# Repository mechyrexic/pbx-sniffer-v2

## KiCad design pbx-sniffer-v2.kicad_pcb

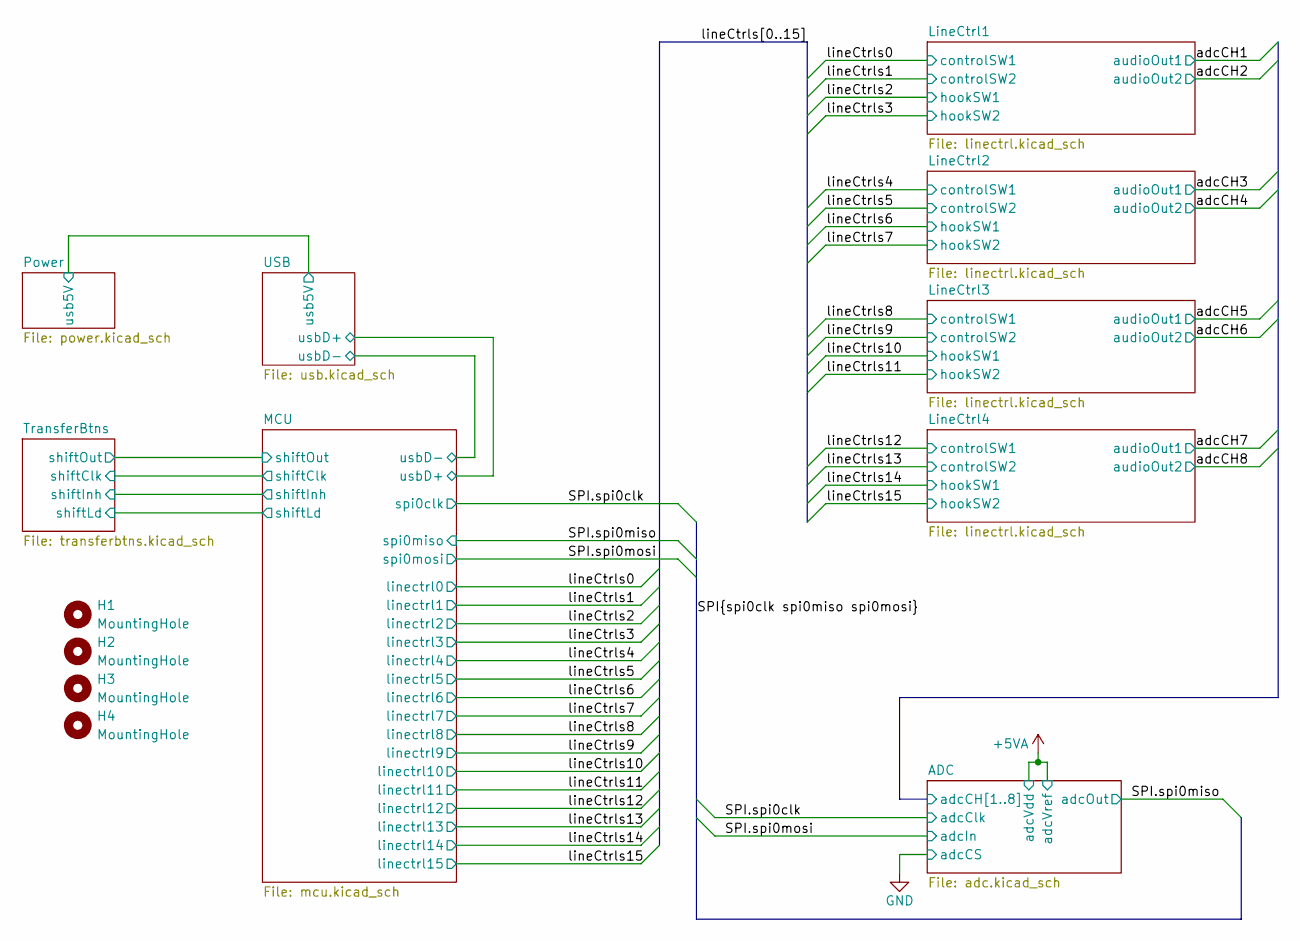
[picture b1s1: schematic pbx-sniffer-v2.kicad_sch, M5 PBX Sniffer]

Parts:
H1, H2, H3, H4: MountingHole; MountingHole_5.3mm_M5_Pad

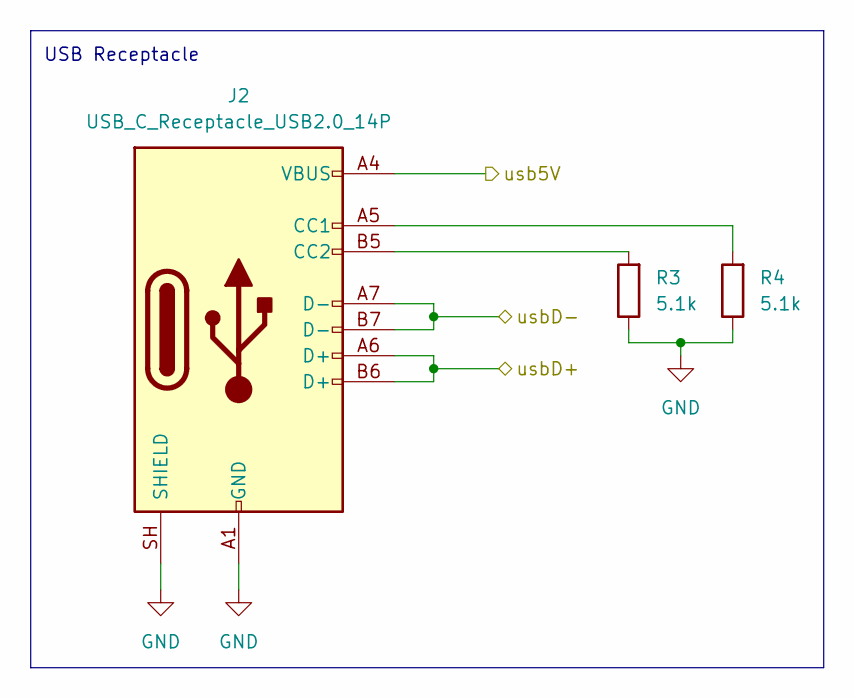
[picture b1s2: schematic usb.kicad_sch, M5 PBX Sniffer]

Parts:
J2: USB_C_Receptacle_USB2.0_14P; USB_C_Receptacle_Amphenol_12401610E4-2A
R3, R4: 5.1k; R_0805_2012Metric

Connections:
/MCU/usbD+: J2.A6 (D+), J2.B6 (D+); also elsewhere on the board
/MCU/usbD-: J2.A7 (D-), J2.B7 (D-); also elsewhere on the board
/Power/usb5V: J2.A4 (VBUS), J2.A9 (VBUS), J2.B4 (VBUS), J2.B9 (VBUS); also elsewhere on the board
GND: J2.A1 (GND), J2.A12 (GND), J2.B1 (GND), J2.B12 (GND), J2.SH (SHIELD), R3.1, R4.1; also elsewhere on the board
unnamed: J2.A5 (CC1), R4.2
unnamed: J2.B5 (CC2), R3.2

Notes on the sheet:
USB Receptacle

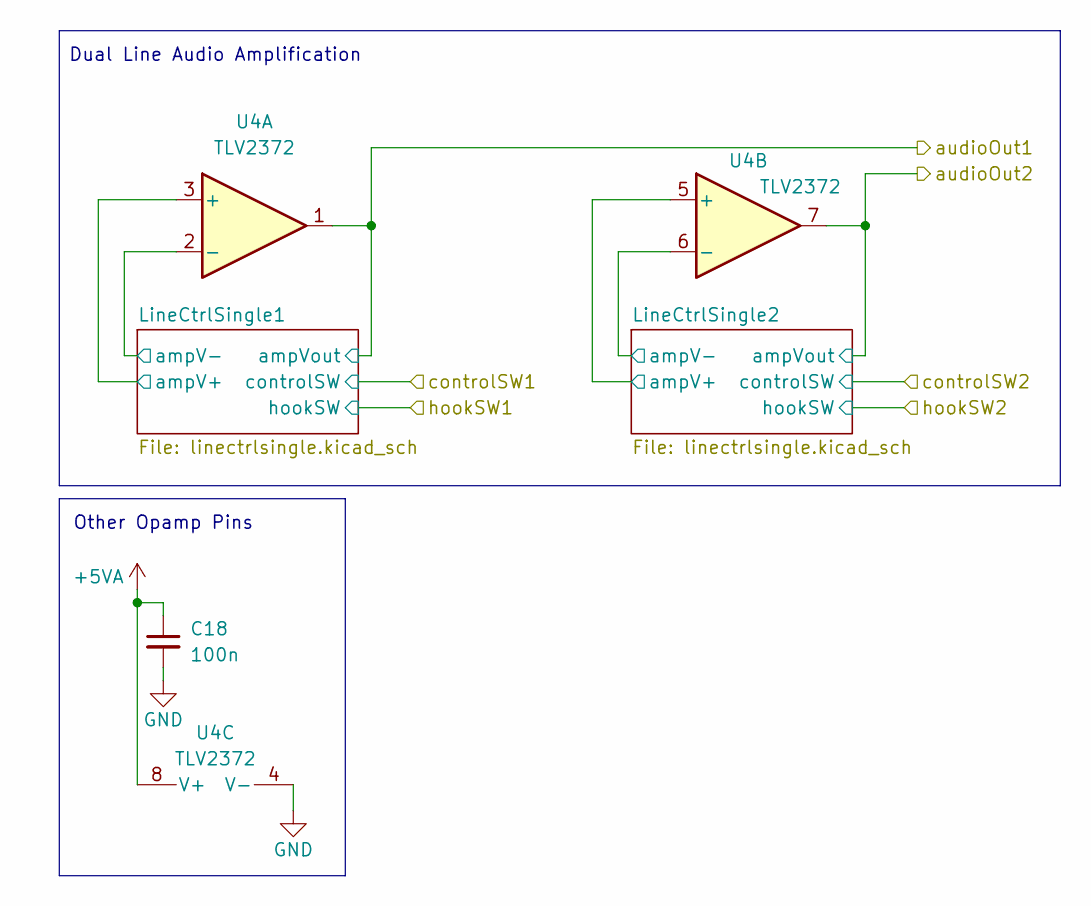
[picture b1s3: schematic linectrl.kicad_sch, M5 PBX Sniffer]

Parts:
C18: 100n; C_0805_2012Metric
U4: TLV2372; SOIC-8_3.9x4.9mm_P1.27mm

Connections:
+5VA: C18.1, U4.8 (V+); also elsewhere on the board
/ADC/adcCH1: U4.1; also elsewhere on the board
/ADC/adcCH2: U4.7; also elsewhere on the board
/LineCtrl1/LineCtrlSingle1/ampV+: U4.3 (+); also elsewhere on the board
/LineCtrl1/LineCtrlSingle1/ampV-: U4.2 (-); also elsewhere on the board
/LineCtrl1/LineCtrlSingle2/ampV+: U4.5 (+); also elsewhere on the board
/LineCtrl1/LineCtrlSingle2/ampV-: U4.6 (-); also elsewhere on the board
GND: C18.2, U4.4 (V-); also elsewhere on the board

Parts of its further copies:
C25, C32, C39: 100n; C_0805_2012Metric
U5, U6, U7: TLV2372; SOIC-8_3.9x4.9mm_P1.27mm

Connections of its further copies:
+5VA: C25.1, C32.1, C39.1, U5.8 (V+), U6.8 (V+), U7.8 (V+); also elsewhere on the board
/ADC/adcCH3: U5.1; also elsewhere on the board
/ADC/adcCH4: U5.7; also elsewhere on the board
/ADC/adcCH5: U6.1; also elsewhere on the board
/ADC/adcCH6: U6.7; also elsewhere on the board
/ADC/adcCH7: U7.1; also elsewhere on the board
/ADC/adcCH8: U7.7; also elsewhere on the board
/LineCtrl2/LineCtrlSingle1/ampV+: U5.3 (+); also elsewhere on the board
/LineCtrl2/LineCtrlSingle1/ampV-: U5.2 (-); also elsewhere on the board
/LineCtrl2/LineCtrlSingle2/ampV+: U5.5 (+); also elsewhere on the board
/LineCtrl2/LineCtrlSingle2/ampV-: U5.6 (-); also elsewhere on the board
/LineCtrl3/LineCtrlSingle1/ampV+: U6.3 (+); also elsewhere on the board
/LineCtrl3/LineCtrlSingle1/ampV-: U6.2 (-); also elsewhere on the board
/LineCtrl3/LineCtrlSingle2/ampV+: U6.5 (+); also elsewhere on the board
/LineCtrl3/LineCtrlSingle2/ampV-: U6.6 (-); also elsewhere on the board
/LineCtrl4/LineCtrlSingle1/ampV+: U7.3 (+); also elsewhere on the board
/LineCtrl4/LineCtrlSingle1/ampV-: U7.2 (-); also elsewhere on the board
/LineCtrl4/LineCtrlSingle2/ampV+: U7.5 (+); also elsewhere on the board
/LineCtrl4/LineCtrlSingle2/ampV-: U7.6 (-); also elsewhere on the board
GND: C25.2, C32.2, C39.2, U5.4 (V-), U6.4 (V-), U7.4 (V-); also elsewhere on the board

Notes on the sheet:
Other Opamp Pins
Dual Line Audio Amplification

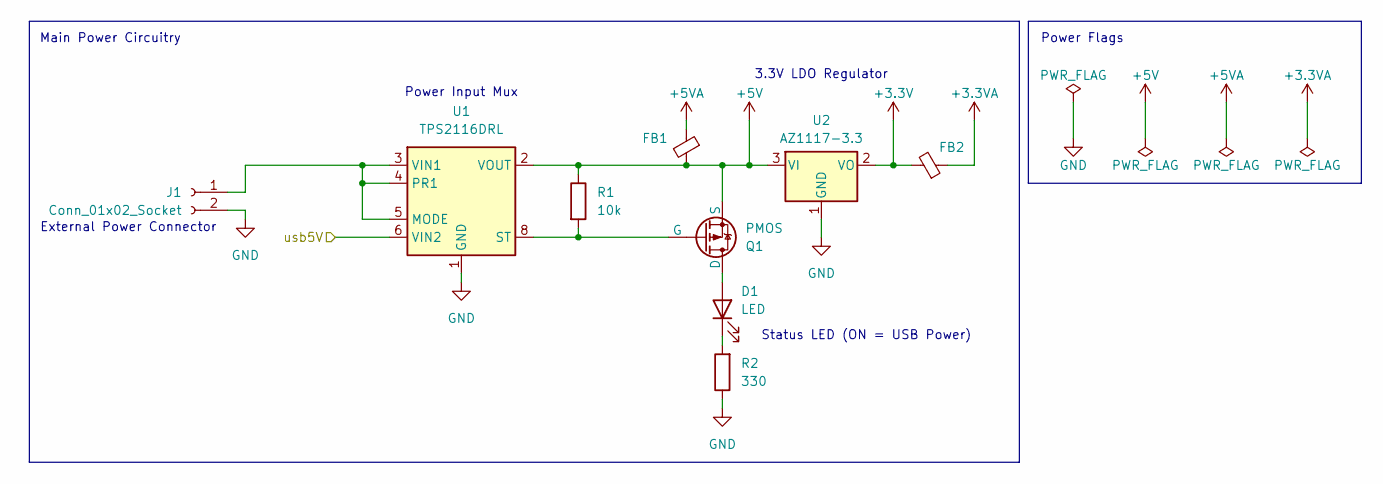
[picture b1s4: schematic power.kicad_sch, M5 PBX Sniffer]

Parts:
D1: LED; R_0603_1608Metric
FB1, FB2: FerriteBead_Small; L_0805_2012Metric
J1: Conn_01x02_Socket; TerminalBlock_CUI_TB007-508-02_1x02_P5.08mm_Horizontal
Q1: PMOS; SOT-23
R1: 10k; R_0805_2012Metric
R2: 330; R_0805_2012Metric
U1: TPS2116DRL; SOT-583-8
U2: AZ1117-3.3; SOT-223

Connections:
+3.3V: FB2.2, U2.2 (VO); also elsewhere on the board
+3.3VA: FB2.1; also elsewhere on the board
+5V: FB1.2, Q1.3 (S), R1.1, U1.2 (VOUT), U1.7 (VOUT), U2.3 (VI); also elsewhere on the board
+5VA: FB1.1; also elsewhere on the board
/Power/usb5V: U1.6 (VIN2); also elsewhere on the board
GND: J1.2, R2.1, U1.1 (GND), U2.1 (GND); also elsewhere on the board
unnamed: D1.2 (A), Q1.1 (D)
unnamed: D1.1 (K), R2.2
unnamed: J1.1, U1.3 (VIN1), U1.4 (PR1), U1.5 (MODE)
unnamed: Q1.2 (G), R1.2, U1.8 (ST)

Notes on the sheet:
3.3V LDO Regulator
Main Power Circuitry
Power Flags
Power Input Mux
Status LED (ON = USB Power)
External Power Connector

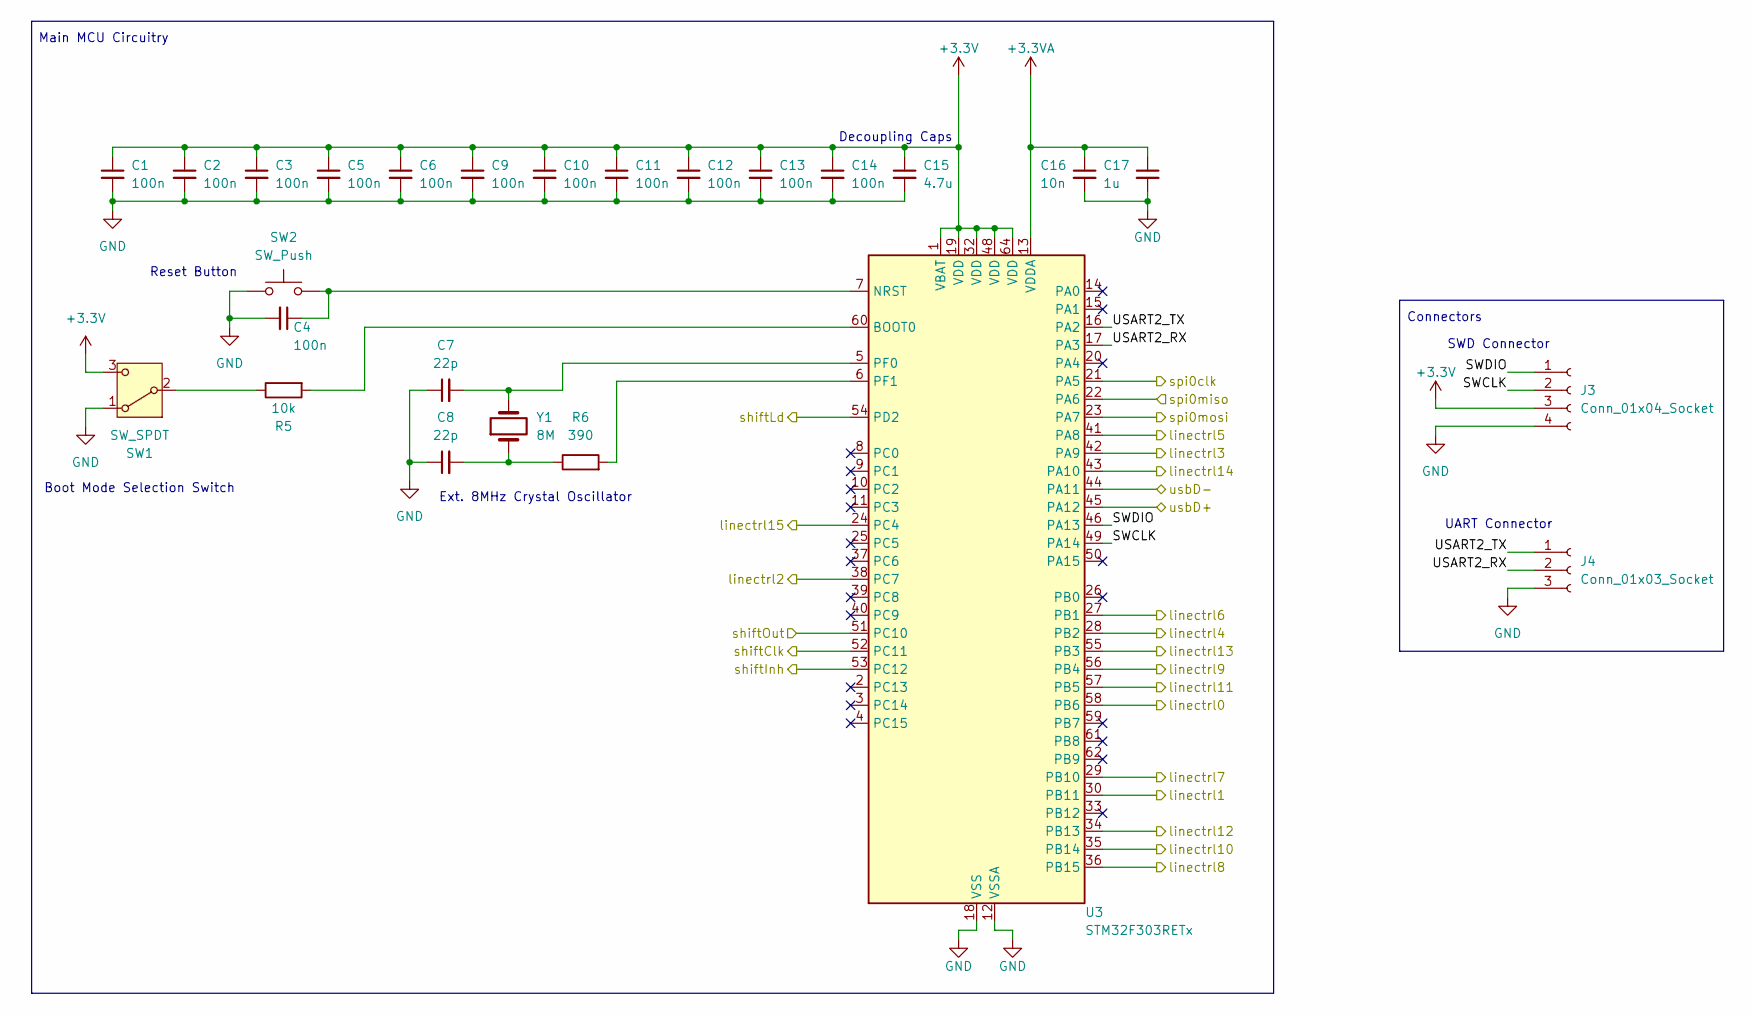
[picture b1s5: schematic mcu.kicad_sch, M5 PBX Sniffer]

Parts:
C1, C2, C3, C4, C5, C6, C9, C10, C11, C12, C13, C14: 100n; C_0805_2012Metric
C7, C8: 22p; C_0805_2012Metric
C15: 4.7u; C_0805_2012Metric
C16: 10n; C_0805_2012Metric
C17: 1u; C_0805_2012Metric
J3: Conn_01x04_Socket; PinHeader_1x04_P2.54mm_Vertical
J4: Conn_01x03_Socket; PinHeader_1x03_P2.54mm_Vertical
R5: 10k; R_0805_2012Metric
R6: 390; R_0805_2012Metric
SW1: SW_SPDT; SW_SPDT_CK_JS102011SAQN
SW2: SW_Push; SW_SPST_PTS647_Sx50
U3: STM32F303RETx; LQFP-64_10x10mm_P0.5mm
Y1: 8M; Crystal_SMD_Abracon_ABM3-2Pin_5.0x3.2mm_HandSoldering

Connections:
+3.3V: C1.1, C2.1, C3.1, C5.1, C6.1, C9.1, C10.1, C11.1, C12.1, C13.1, C14.1, C15.1, J3.3, SW1.3 (C), U3.1 (VBAT), U3.19 (VDD), U3.32 (VDD), U3.48 (VDD), U3.64 (VDD); also elsewhere on the board
+3.3VA: C16.1, C17.1, U3.13 (VDDA); also elsewhere on the board
/MCU/SWCLK: J3.2, U3.49 (PA14)
/MCU/SWDIO: J3.1, U3.46 (PA13)
/MCU/USART2_RX: J4.2, U3.17 (PA3)
/MCU/USART2_TX: J4.1, U3.16 (PA2)
/MCU/shiftClk: U3.52 (PC11); also elsewhere on the board
/MCU/shiftInh: U3.53 (PC12); also elsewhere on the board
/MCU/shiftLd: U3.54 (PD2); also elsewhere on the board
/MCU/shiftOut: U3.51 (PC10); also elsewhere on the board
/MCU/usbD+: U3.45 (PA12); also elsewhere on the board
/MCU/usbD-: U3.44 (PA11); also elsewhere on the board
/SPI.spi0clk: U3.21 (PA5); also elsewhere on the board
/SPI.spi0miso: U3.22 (PA6); also elsewhere on the board
/SPI.spi0mosi: U3.23 (PA7); also elsewhere on the board
/lineCtrls0: U3.58 (PB6); also elsewhere on the board
/lineCtrls1: U3.30 (PB11); also elsewhere on the board
/lineCtrls2: U3.38 (PC7); also elsewhere on the board
/lineCtrls3: U3.42 (PA9); also elsewhere on the board
/lineCtrls4: U3.28 (PB2); also elsewhere on the board
/lineCtrls5: U3.41 (PA8); also elsewhere on the board
/lineCtrls6: U3.27 (PB1); also elsewhere on the board
/lineCtrls7: U3.29 (PB10); also elsewhere on the board
/lineCtrls8: U3.36 (PB15); also elsewhere on the board
/lineCtrls9: U3.56 (PB4); also elsewhere on the board
/lineCtrls10: U3.35 (PB14); also elsewhere on the board
/lineCtrls11: U3.57 (PB5); also elsewhere on the board
/lineCtrls12: U3.34 (PB13); also elsewhere on the board
/lineCtrls13: U3.55 (PB3); also elsewhere on the board
/lineCtrls14: U3.43 (PA10); also elsewhere on the board
/lineCtrls15: U3.24 (PC4); also elsewhere on the board
GND: C1.2, C2.2, C3.2, C4.2, C5.2, C6.2, C7.1, C8.1, C9.2, C10.2, C11.2, C12.2, C13.2, C14.2, C15.2, C16.2, C17.2, J3.4, J4.3, SW1.1 (A), SW2.1, U3.12 (VSSA), U3.18 (VSS), U3.31 (VSS), U3.47 (VSS), U3.63 (VSS); also elsewhere on the board
unnamed: C8.2, R6.1, Y1.1
unnamed: R5.1, SW1.2 (B)
unnamed: R5.2, U3.60 (BOOT0)
unnamed: C4.1, SW2.2, U3.7 (NRST)
unnamed: C7.2, U3.5 (PF0), Y1.2
unnamed: R6.2, U3.6 (PF1)

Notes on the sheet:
SWD Connector
Connectors
Decoupling Caps
Ext. 8MHz Crystal Oscillator
Reset Button
UART Connector
Boot Mode Selection Switch
Main MCU Circuitry

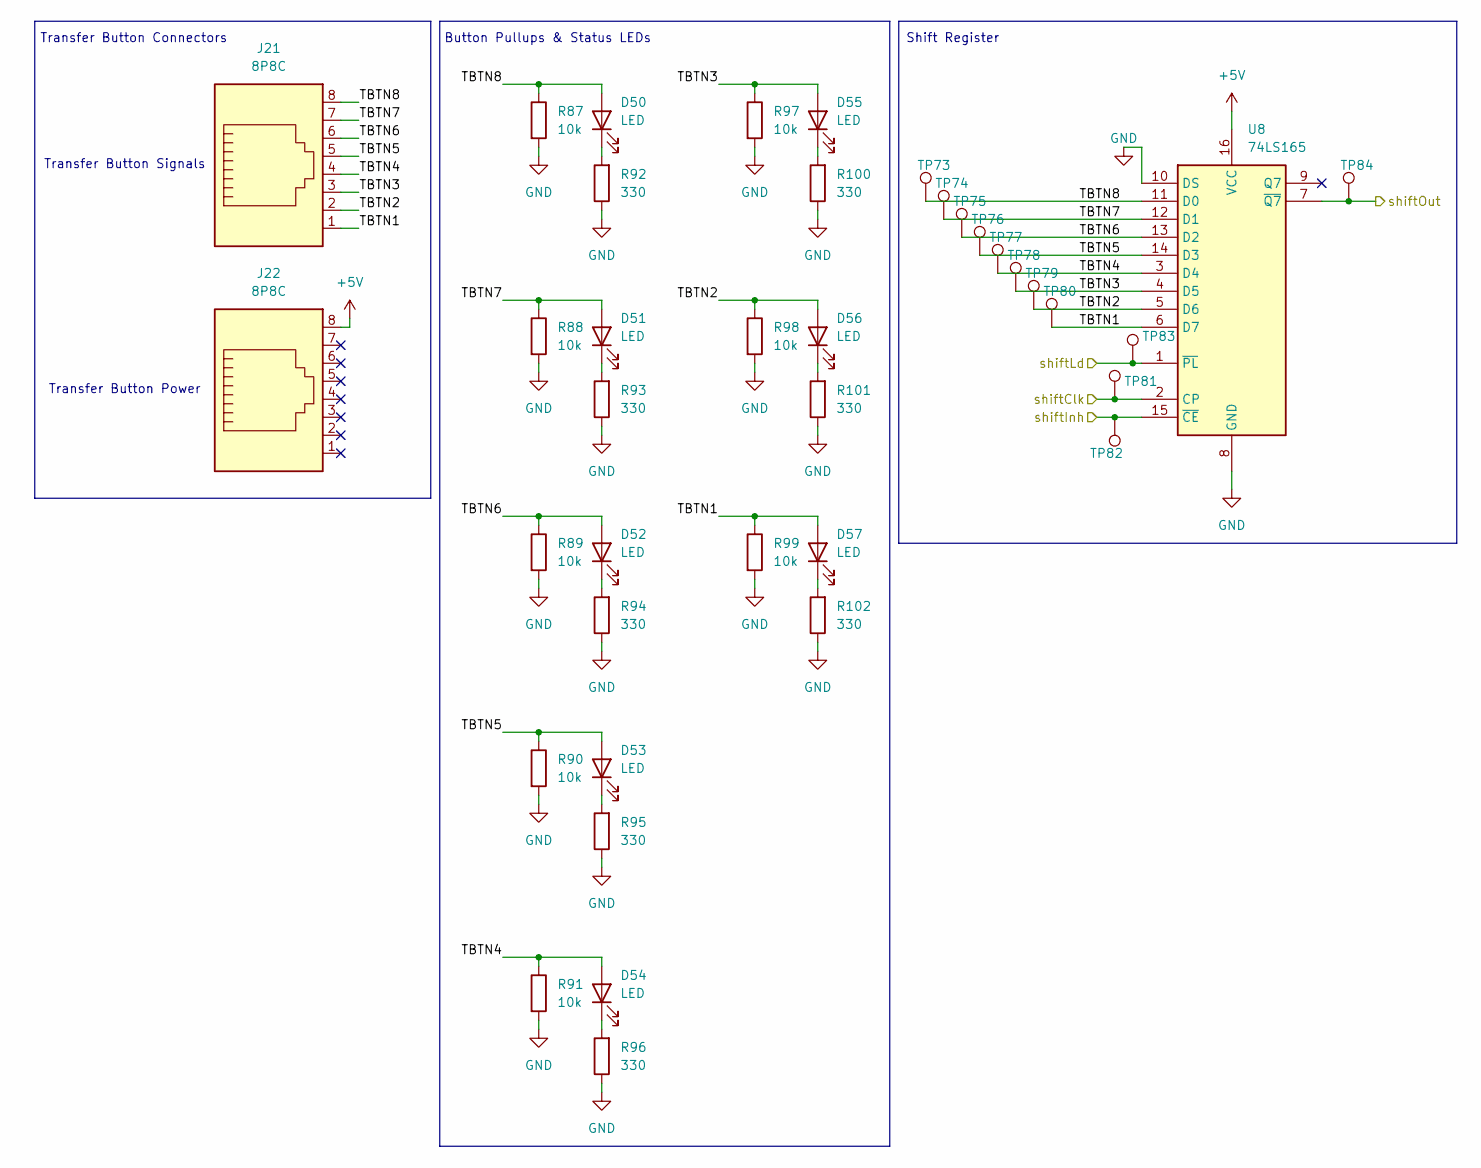
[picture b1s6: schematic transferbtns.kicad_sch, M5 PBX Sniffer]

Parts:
D50, D51, D52, D53, D54, D55, D56, D57: LED; R_0603_1608Metric
J21, J22: 8P8C; AMPHENOL_54602-908LF
R87, R88, R89, R90, R91, R97, R98, R99: 10k; R_0805_2012Metric
R92, R93, R94, R95, R96, R100, R101, R102: 330; R_0805_2012Metric
TP73, TP74, TP75, TP76, TP77, TP78, TP79, TP80, TP81, TP82, TP83, TP84: TestPoint; M5_3in1_TestPoint
U8: 74LS165; TSSOP-16_4.4x5mm_P0.65mm

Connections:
+5V: J22.8, U8.16 (VCC); also elsewhere on the board
/MCU/shiftClk: TP81.1 (1_1), U8.2 (CP); also elsewhere on the board
/MCU/shiftInh: TP82.1 (1_1), U8.15 (~CE); also elsewhere on the board
/MCU/shiftLd: TP83.1 (1_1), U8.1 (~PL); also elsewhere on the board
/MCU/shiftOut: TP84.1 (1_1), U8.7 (~Q7); also elsewhere on the board
/TransferBtns/TBTN1: D57.2 (A), J21.1, R99.1, TP80.1 (1_1), U8.6 (D7)
/TransferBtns/TBTN2: D56.2 (A), J21.2, R98.1, TP79.1 (1_1), U8.5 (D6)
/TransferBtns/TBTN3: D55.2 (A), J21.3, R97.1, TP78.1 (1_1), U8.4 (D5)
/TransferBtns/TBTN4: D54.2 (A), J21.4, R91.1, TP77.1 (1_1), U8.3 (D4)
/TransferBtns/TBTN5: D53.2 (A), J21.5, R90.1, TP76.1 (1_1), U8.14 (D3)
/TransferBtns/TBTN6: D52.2 (A), J21.6, R89.1, TP75.1 (1_1), U8.13 (D2)
/TransferBtns/TBTN7: D51.2 (A), J21.7, R88.1, TP74.1 (1_1), U8.12 (D1)
/TransferBtns/TBTN8: D50.2 (A), J21.8, R87.1, TP73.1 (1_1), U8.11 (D0)
GND: R87.2, R88.2, R89.2, R90.2, R91.2, R92.1, R93.1, R94.1, R95.1, R96.1, R97.2, R98.2, R99.2, R100.1, R101.1, R102.1, U8.8 (GND), U8.10 (DS); also elsewhere on the board
unnamed: D50.1 (K), R92.2
unnamed: D51.1 (K), R93.2
unnamed: D52.1 (K), R94.2
unnamed: D53.1 (K), R95.2
unnamed: D54.1 (K), R96.2
unnamed: D55.1 (K), R100.2
unnamed: D56.1 (K), R101.2
unnamed: D57.1 (K), R102.2

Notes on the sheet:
Transfer Button Power
Transfer Button Connectors
Shift Register
Button Pullups & Status LEDs
Transfer Button Signals

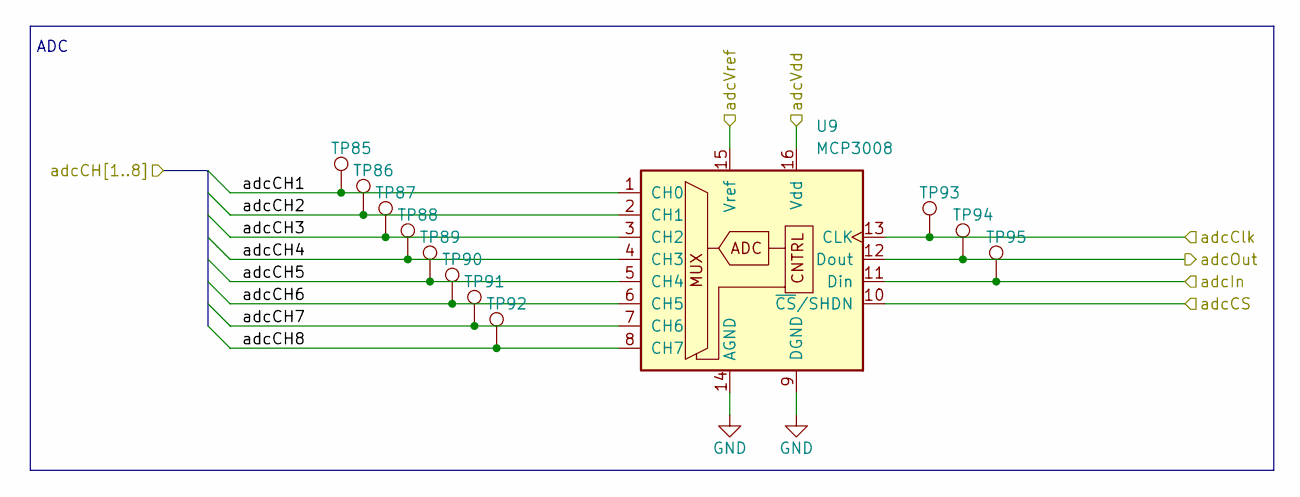
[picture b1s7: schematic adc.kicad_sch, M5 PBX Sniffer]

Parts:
TP85, TP86, TP87, TP88, TP89, TP90, TP91, TP92, TP93, TP94, TP95: TestPoint; M5_3in1_TestPoint
U9: MCP3008; SOIC-16_3.9x9.9mm_P1.27mm

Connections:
+5VA: U9.15 (Vref), U9.16 (Vdd); also elsewhere on the board
/ADC/adcCH1: TP85.1 (1_1), U9.1 (CH0); also elsewhere on the board
/ADC/adcCH2: TP86.1 (1_1), U9.2 (CH1); also elsewhere on the board
/ADC/adcCH3: TP87.1 (1_1), U9.3 (CH2); also elsewhere on the board
/ADC/adcCH4: TP88.1 (1_1), U9.4 (CH3); also elsewhere on the board
/ADC/adcCH5: TP89.1 (1_1), U9.5 (CH4); also elsewhere on the board
/ADC/adcCH6: TP90.1 (1_1), U9.6 (CH5); also elsewhere on the board
/ADC/adcCH7: TP91.1 (1_1), U9.7 (CH6); also elsewhere on the board
/ADC/adcCH8: TP92.1 (1_1), U9.8 (CH7); also elsewhere on the board
/SPI.spi0clk: TP93.1 (1_1), U9.13 (CLK); also elsewhere on the board
/SPI.spi0miso: TP94.1 (1_1), U9.12 (Dout); also elsewhere on the board
/SPI.spi0mosi: TP95.1 (1_1), U9.11 (Din); also elsewhere on the board
GND: U9.9 (DGND), U9.10 (~CS/SHDN), U9.14 (AGND); also elsewhere on the board

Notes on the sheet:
ADC

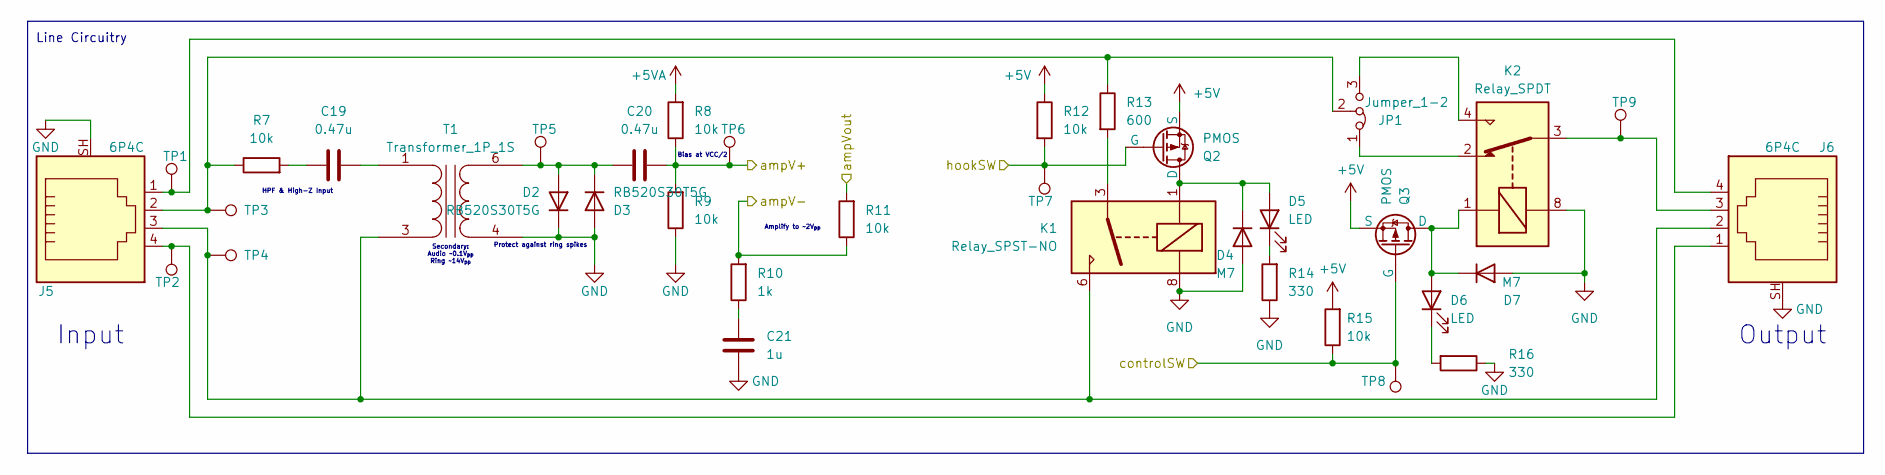
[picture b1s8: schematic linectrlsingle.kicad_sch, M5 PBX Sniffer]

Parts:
C19, C20: 0.47u; C_0805_2012Metric
C21: 1u; C_0805_2012Metric
D2, D3: RB520S30T5G; D_SOD-523
D4, D7: M7; D_SMA
D5, D6: LED; R_0603_1608Metric
J5, J6: 6P4C; CUI_CRJ050-1-TH
JP1: Jumper_1-2; SolderJumper-3_P1.3mm_Bridged2Bar12_RoundedPad1.0x1.5mm
K1: Relay_SPST-NO; Relay_2P2T_10x6mm_TE_IMxxG
K2: Relay_SPDT; Relay_2P2T_10x6mm_TE_IMxxG
Q2, Q3: PMOS; SOT-23
R7, R8, R9, R11, R12, R15: 10k; R_0805_2012Metric
R10: 1k; R_0805_2012Metric
R13: 600; R_0805_2012Metric
R14, R16: 330; R_0805_2012Metric
T1: Transformer_1P_1S; TRAN6_SM-LP-5001_BRN
TP1, TP2, TP3, TP4, TP5, TP6, TP7, TP8, TP9: TestPoint; M5_3in1_TestPoint

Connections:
+5V: Q2.3 (S), Q3.3 (S), R12.1, R15.2; also elsewhere on the board
+5VA: R8.2; also elsewhere on the board
/ADC/adcCH1: R11.2; also elsewhere on the board
/LineCtrl1/LineCtrlSingle1/ampV+: C20.2, R8.1, R9.2, TP6.1 (1_1); also elsewhere on the board
/LineCtrl1/LineCtrlSingle1/ampV-: R10.2, R11.1; also elsewhere on the board
/lineCtrls0: Q3.2 (G), R15.1, TP8.1 (1_1); also elsewhere on the board
/lineCtrls2: Q2.2 (G), R12.2, TP7.1 (1_1); also elsewhere on the board
GND: C21.1, D2.1 (K), D3.2 (A), D4.2 (A), D7.2 (A), J5.SH, J6.SH, K1.8, K2.8, R9.1, R14.1, R16.1, T1.4 (SA); also elsewhere on the board
unnamed: C19.1, R7.2
unnamed: C21.2, R10.1
unnamed: C20.1, D2.2 (A), D3.1 (K), T1.6 (SB), TP5.1 (1_1)
unnamed: D4.1 (K), D5.2 (A), K1.1, Q2.1 (D)
unnamed: D5.1 (K), R14.2
unnamed: D6.2 (A), D7.1 (K), K2.1, Q3.1 (D)
unnamed: D6.1 (K), R16.2
unnamed: J5.1, J6.4, TP1.1 (1_1)
unnamed: J5.4, J6.1, TP2.1 (1_1)
unnamed: J6.3, K2.3, TP9.1 (1_1)
unnamed: JP1.1 (A), K2.2
unnamed: JP1.3 (B), K2.4
unnamed: J5.2, JP1.2 (C), R7.1, R13.1, TP3.1 (1_1)
unnamed: K1.3, R13.2
unnamed: C19.2, T1.1 (AA)
unnamed: J5.3, J6.2, K1.6, T1.3 (AB), TP4.1 (1_1)

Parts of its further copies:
C22, C23, C26, C27, C29, C30, C33, C34, C36, C37, C40, C41, C43, C44: 0.47u; C_0805_2012Metric
C24, C28, C31, C35, C38, C42, C45: 1u; C_0805_2012Metric
D8, D9, D14, D15, D20, D21, D26, D27, D32, D33, D38, D39, D44, D45: RB520S30T5G; D_SOD-523
D10, D13, D16, D19, D22, D25, D28, D31, D34, D37, D40, D43, D46, D49: M7; D_SMA
D11, D12, D17, D18, D23, D24, D29, D30, D35, D36, D41, D42, D47, D48: LED; R_0603_1608Metric
J7, J8, J9, J10, J11, J12, J13, J14, J15, J16, J17, J18, J19, J20: 6P4C; CUI_CRJ050-1-TH
JP2, JP3, JP4, JP5, JP6, JP7, JP8: Jumper_1-2; SolderJumper-3_P1.3mm_Bridged2Bar12_RoundedPad1.0x1.5mm
K3, K5, K7, K9, K11, K13, K15: Relay_SPST-NO; Relay_2P2T_10x6mm_TE_IMxxG
K4, K6, K8, K10, K12, K14, K16: Relay_SPDT; Relay_2P2T_10x6mm_TE_IMxxG
Q4, Q5, Q6, Q7, Q8, Q9, Q10, Q11, Q12, Q13, Q14, Q15, Q16, Q17: PMOS; SOT-23
R17, R18, R19, R21, R22, R25, R27, R28, R29, R31, R32, R35, R37, R38, R39, R41, R42, R45, R47, R48, R49, R51, R52, R55, R57, R58, R59, R61, R62, R65, R67, R68, R69, R71, R72, R75, R77, R78, R79, R81, R82, R85: 10k; R_0805_2012Metric
R20, R30, R40, R50, R60, R70, R80: 1k; R_0805_2012Metric
R23, R33, R43, R53, R63, R73, R83: 600; R_0805_2012Metric
R24, R26, R34, R36, R44, R46, R54, R56, R64, R66, R74, R76, R84, R86: 330; R_0805_2012Metric
T2, T3, T4, T5, T6, T7, T8: Transformer_1P_1S; TRAN6_SM-LP-5001_BRN
TP10, TP11, TP12, TP13, TP14, TP15, TP16, TP17, TP18, TP19, TP20, TP21, TP22, TP23, TP24, TP25, TP26, TP27, TP28, TP29, TP30, TP31, TP32, TP33, TP34, TP35, TP36, TP37, TP38, TP39, TP40, TP41, TP42, TP43, TP44, TP45, TP46, TP47, TP48, TP49, TP50, TP51, TP52, TP53, TP54, TP55, TP56, TP57, TP58, TP59, TP60, TP61, TP62, TP63, TP64, TP65, TP66, TP67, TP68, TP69, TP70, TP71, TP72: TestPoint; M5_3in1_TestPoint

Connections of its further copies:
+5V: Q4.3 (S), Q5.3 (S), Q6.3 (S), Q7.3 (S), Q8.3 (S), Q9.3 (S), Q10.3 (S), Q11.3 (S), Q12.3 (S), Q13.3 (S), Q14.3 (S), Q15.3 (S), Q16.3 (S), Q17.3 (S), R22.1, R25.2, R32.1, R35.2, R42.1, R45.2, R52.1, R55.2, R62.1, R65.2, R72.1, R75.2, R82.1, R85.2; also elsewhere on the board
+5VA: R18.2, R28.2, R38.2, R48.2, R58.2, R68.2, R78.2; also elsewhere on the board
/ADC/adcCH2: R21.2; also elsewhere on the board
/ADC/adcCH3: R31.2; also elsewhere on the board
/ADC/adcCH4: R41.2; also elsewhere on the board
/ADC/adcCH5: R51.2; also elsewhere on the board
/ADC/adcCH6: R61.2; also elsewhere on the board
/ADC/adcCH7: R71.2; also elsewhere on the board
/ADC/adcCH8: R81.2; also elsewhere on the board
/LineCtrl1/LineCtrlSingle2/ampV+: C23.2, R18.1, R19.2, TP15.1 (1_1); also elsewhere on the board
/LineCtrl1/LineCtrlSingle2/ampV-: R20.2, R21.1; also elsewhere on the board
/LineCtrl2/LineCtrlSingle1/ampV+: C27.2, R28.1, R29.2, TP24.1 (1_1); also elsewhere on the board
/LineCtrl2/LineCtrlSingle1/ampV-: R30.2, R31.1; also elsewhere on the board
/LineCtrl2/LineCtrlSingle2/ampV+: C30.2, R38.1, R39.2, TP33.1 (1_1); also elsewhere on the board
/LineCtrl2/LineCtrlSingle2/ampV-: R40.2, R41.1; also elsewhere on the board
/LineCtrl3/LineCtrlSingle1/ampV+: C34.2, R48.1, R49.2, TP42.1 (1_1); also elsewhere on the board
/LineCtrl3/LineCtrlSingle1/ampV-: R50.2, R51.1; also elsewhere on the board
/LineCtrl3/LineCtrlSingle2/ampV+: C37.2, R58.1, R59.2, TP51.1 (1_1); also elsewhere on the board
/LineCtrl3/LineCtrlSingle2/ampV-: R60.2, R61.1; also elsewhere on the board
/LineCtrl4/LineCtrlSingle1/ampV+: C41.2, R68.1, R69.2, TP60.1 (1_1); also elsewhere on the board
/LineCtrl4/LineCtrlSingle1/ampV-: R70.2, R71.1; also elsewhere on the board
/LineCtrl4/LineCtrlSingle2/ampV+: C44.2, R78.1, R79.2, TP69.1 (1_1); also elsewhere on the board
/LineCtrl4/LineCtrlSingle2/ampV-: R80.2, R81.1; also elsewhere on the board
/lineCtrls1: Q5.2 (G), R25.1, TP17.1 (1_1); also elsewhere on the board
/lineCtrls3: Q4.2 (G), R22.2, TP16.1 (1_1); also elsewhere on the board
/lineCtrls4: Q7.2 (G), R35.1, TP26.1 (1_1); also elsewhere on the board
/lineCtrls5: Q9.2 (G), R45.1, TP35.1 (1_1); also elsewhere on the board
/lineCtrls6: Q6.2 (G), R32.2, TP25.1 (1_1); also elsewhere on the board
/lineCtrls7: Q8.2 (G), R42.2, TP34.1 (1_1); also elsewhere on the board
/lineCtrls8: Q11.2 (G), R55.1, TP44.1 (1_1); also elsewhere on the board
/lineCtrls9: Q13.2 (G), R65.1, TP53.1 (1_1); also elsewhere on the board
/lineCtrls10: Q10.2 (G), R52.2, TP43.1 (1_1); also elsewhere on the board
/lineCtrls11: Q12.2 (G), R62.2, TP52.1 (1_1); also elsewhere on the board
/lineCtrls12: Q15.2 (G), R75.1, TP62.1 (1_1); also elsewhere on the board
/lineCtrls13: Q17.2 (G), R85.1, TP71.1 (1_1); also elsewhere on the board
/lineCtrls14: Q14.2 (G), R72.2, TP61.1 (1_1); also elsewhere on the board
/lineCtrls15: Q16.2 (G), R82.2, TP70.1 (1_1); also elsewhere on the board
GND: C24.1, C28.1, C31.1, C35.1, C38.1, C42.1, C45.1, D8.1 (K), D9.2 (A), D10.2 (A), D13.2 (A), D14.1 (K), D15.2 (A), D16.2 (A), D19.2 (A), D20.1 (K), D21.2 (A), D22.2 (A), D25.2 (A), D26.1 (K), D27.2 (A), D28.2 (A), D31.2 (A), D32.1 (K), D33.2 (A), D34.2 (A), D37.2 (A), D38.1 (K), D39.2 (A), D40.2 (A), D43.2 (A), D44.1 (K), D45.2 (A), D46.2 (A), D49.2 (A), J7.SH, J8.SH, J9.SH, J10.SH, J11.SH, J12.SH, J13.SH, J14.SH, J15.SH, J16.SH, J17.SH, J18.SH, J19.SH, J20.SH, K3.8, K4.8, K5.8, K6.8, K7.8, K8.8, K9.8, K10.8, K11.8, K12.8, K13.8, K14.8, K15.8, K16.8, R19.1, R24.1, R26.1, R29.1, R34.1, R36.1, R39.1, R44.1, R46.1, R49.1, R54.1, R56.1, R59.1, R64.1, R66.1, R69.1, R74.1, R76.1, R79.1, R84.1, R86.1, T2.4 (SA), T3.4 (SA), T4.4 (SA), T5.4 (SA), T6.4 (SA), T7.4 (SA), T8.4 (SA); also elsewhere on the board
unnamed: C22.1, R17.2
unnamed: C24.2, R20.1
unnamed: C26.1, R27.2
unnamed: C28.2, R30.1
unnamed: C29.1, R37.2
unnamed: C31.2, R40.1
unnamed: C33.1, R47.2
unnamed: C35.2, R50.1
unnamed: C36.1, R57.2
unnamed: C38.2, R60.1
unnamed: C40.1, R67.2
unnamed: C42.2, R70.1
unnamed: C43.1, R77.2
unnamed: C45.2, R80.1
unnamed: C23.1, D8.2 (A), D9.1 (K), T2.6 (SB), TP14.1 (1_1)
unnamed: D10.1 (K), D11.2 (A), K3.1, Q4.1 (D)
unnamed: D11.1 (K), R24.2
unnamed: D12.2 (A), D13.1 (K), K4.1, Q5.1 (D)
unnamed: D12.1 (K), R26.2
unnamed: C27.1, D14.2 (A), D15.1 (K), T3.6 (SB), TP23.1 (1_1)
unnamed: D16.1 (K), D17.2 (A), K5.1, Q6.1 (D)
unnamed: D17.1 (K), R34.2
unnamed: D18.2 (A), D19.1 (K), K6.1, Q7.1 (D)
unnamed: D18.1 (K), R36.2
unnamed: C30.1, D20.2 (A), D21.1 (K), T4.6 (SB), TP32.1 (1_1)
unnamed: D22.1 (K), D23.2 (A), K7.1, Q8.1 (D)
unnamed: D23.1 (K), R44.2
unnamed: D24.2 (A), D25.1 (K), K8.1, Q9.1 (D)
unnamed: D24.1 (K), R46.2
unnamed: C34.1, D26.2 (A), D27.1 (K), T5.6 (SB), TP41.1 (1_1)
unnamed: D28.1 (K), D29.2 (A), K9.1, Q10.1 (D)
unnamed: D29.1 (K), R54.2
unnamed: D30.2 (A), D31.1 (K), K10.1, Q11.1 (D)
unnamed: D30.1 (K), R56.2
unnamed: C37.1, D32.2 (A), D33.1 (K), T6.6 (SB), TP50.1 (1_1)
unnamed: D34.1 (K), D35.2 (A), K11.1, Q12.1 (D)
unnamed: D35.1 (K), R64.2
unnamed: D36.2 (A), D37.1 (K), K12.1, Q13.1 (D)
unnamed: D36.1 (K), R66.2
unnamed: C41.1, D38.2 (A), D39.1 (K), T7.6 (SB), TP59.1 (1_1)
unnamed: D40.1 (K), D41.2 (A), K13.1, Q14.1 (D)
unnamed: D41.1 (K), R74.2
unnamed: D42.2 (A), D43.1 (K), K14.1, Q15.1 (D)
unnamed: D42.1 (K), R76.2
unnamed: C44.1, D44.2 (A), D45.1 (K), T8.6 (SB), TP68.1 (1_1)
unnamed: D46.1 (K), D47.2 (A), K15.1, Q16.1 (D)
unnamed: D47.1 (K), R84.2
unnamed: D48.2 (A), D49.1 (K), K16.1, Q17.1 (D)
unnamed: D48.1 (K), R86.2
unnamed: J7.1, J8.4, TP10.1 (1_1)
unnamed: J7.4, J8.1, TP11.1 (1_1)
unnamed: J8.3, K4.3, TP18.1 (1_1)
unnamed: J9.4, J10.1, TP20.1 (1_1)
unnamed: J10.3, K6.3, TP27.1 (1_1)
unnamed: J9.1, J10.4, TP19.1 (1_1)
unnamed: J11.1, J12.4, TP28.1 (1_1)
unnamed: J11.4, J12.1, TP29.1 (1_1)
unnamed: J12.3, K8.3, TP36.1 (1_1)
unnamed: J13.1, J14.4, TP37.1 (1_1)
unnamed: J13.4, J14.1, TP38.1 (1_1)
unnamed: J14.3, K10.3, TP45.1 (1_1)
unnamed: J15.1, J16.4, TP46.1 (1_1)
unnamed: J15.4, J16.1, TP47.1 (1_1)
unnamed: J16.3, K12.3, TP54.1 (1_1)
unnamed: J17.1, J18.4, TP55.1 (1_1)
unnamed: J17.4, J18.1, TP56.1 (1_1)
unnamed: J18.3, K14.3, TP63.1 (1_1)
unnamed: J19.1, J20.4, TP64.1 (1_1)
unnamed: J19.4, J20.1, TP65.1 (1_1)
unnamed: J20.3, K16.3, TP72.1 (1_1)
unnamed: JP2.1 (A), K4.2
unnamed: JP2.3 (B), K4.4
unnamed: J7.2, JP2.2 (C), R17.1, R23.1, TP12.1 (1_1)
unnamed: JP3.1 (A), K6.2
unnamed: JP3.3 (B), K6.4
unnamed: J9.2, JP3.2 (C), R27.1, R33.1, TP21.1 (1_1)
unnamed: JP4.1 (A), K8.2
unnamed: JP4.3 (B), K8.4
unnamed: J11.2, JP4.2 (C), R37.1, R43.1, TP30.1 (1_1)
unnamed: JP5.1 (A), K10.2
unnamed: JP5.3 (B), K10.4
unnamed: J13.2, JP5.2 (C), R47.1, R53.1, TP39.1 (1_1)
unnamed: JP6.1 (A), K12.2
unnamed: JP6.3 (B), K12.4
unnamed: J15.2, JP6.2 (C), R57.1, R63.1, TP48.1 (1_1)
unnamed: JP7.1 (A), K14.2
unnamed: JP7.3 (B), K14.4
unnamed: J17.2, JP7.2 (C), R67.1, R73.1, TP57.1 (1_1)
unnamed: JP8.1 (A), K16.2
unnamed: JP8.3 (B), K16.4
unnamed: J19.2, JP8.2 (C), R77.1, R83.1, TP66.1 (1_1)
unnamed: K3.3, R23.2
unnamed: K5.3, R33.2
unnamed: K7.3, R43.2
unnamed: K9.3, R53.2
unnamed: K11.3, R63.2
unnamed: K13.3, R73.2
unnamed: K15.3, R83.2
unnamed: C22.2, T2.1 (AA)
unnamed: J7.3, J8.2, K3.6, T2.3 (AB), TP13.1 (1_1)
unnamed: C26.2, T3.1 (AA)
unnamed: J9.3, J10.2, K5.6, T3.3 (AB), TP22.1 (1_1)
unnamed: C29.2, T4.1 (AA)
unnamed: J11.3, J12.2, K7.6, T4.3 (AB), TP31.1 (1_1)
unnamed: C33.2, T5.1 (AA)
unnamed: J13.3, J14.2, K9.6, T5.3 (AB), TP40.1 (1_1)
unnamed: C36.2, T6.1 (AA)
unnamed: J15.3, J16.2, K11.6, T6.3 (AB), TP49.1 (1_1)
unnamed: C40.2, T7.1 (AA)
unnamed: J17.3, J18.2, K13.6, T7.3 (AB), TP58.1 (1_1)
unnamed: C43.2, T8.1 (AA)
unnamed: J19.3, J20.2, K15.6, T8.3 (AB), TP67.1 (1_1)

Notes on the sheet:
Line Circuitry
Output
Input
Secondary: Audio ~0.1V_{pp} Ring ~14V_{pp}
Protect against ring spikes
HPF & High-Z Input
Amplify to ~2V_{pp}
Bias at VCC/2

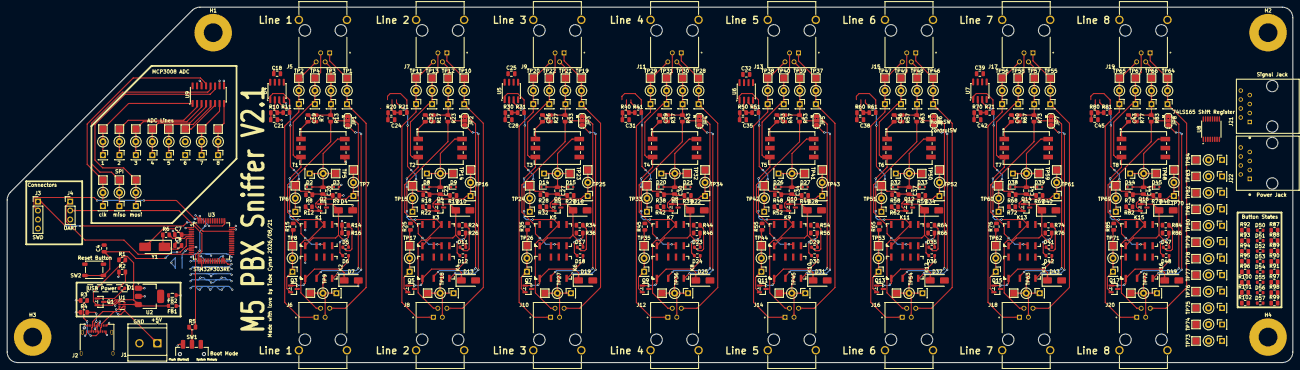
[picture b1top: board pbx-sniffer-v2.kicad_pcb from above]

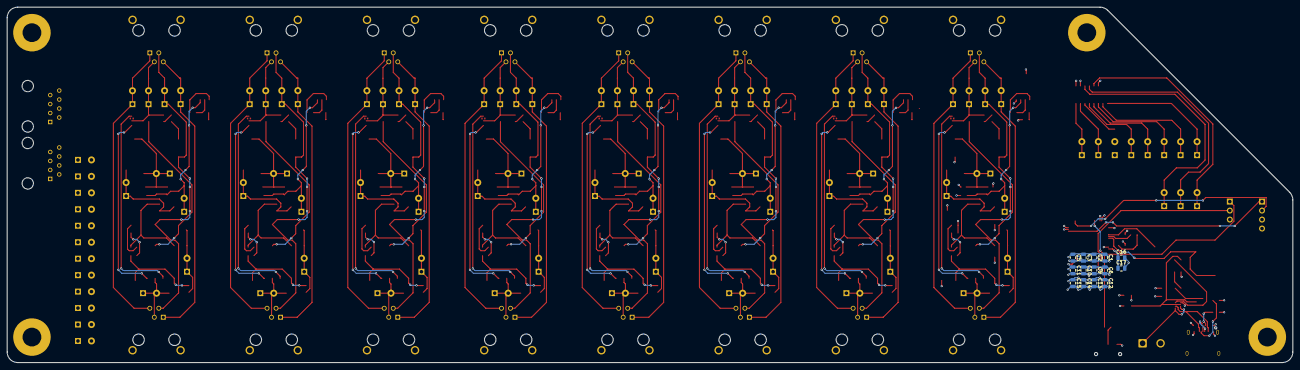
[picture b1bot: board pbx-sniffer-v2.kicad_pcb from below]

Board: 4 copper layers, 363.2 x 100.4 mm, 388 parts (14 on the bottom side), 215 nets.

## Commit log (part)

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2026-06-02 first iteration of line control schematic
2026-06-02 finish linectrl implementation
2026-06-02 add transfer buttons subsheet
2026-06-02 start connecting subsheets to main schematic
2026-06-03 finish schematic capture
2026-06-03 add test points throughout the schematic
2026-06-03 finish initial schematic design, start pcb layout
2026-06-03 continue pcb layout, finish linectrl layout
2026-06-04 make each phone line a subsheet and start redoing layout
2026-06-04 place footprints for one line module
2026-06-04 layout and replicate remaining lines
2026-06-04 convert to 4 layer board and add power/gnd planes
2026-06-08 fix controlsw/hooksw subsheet error
2026-06-08 finish initial layout
